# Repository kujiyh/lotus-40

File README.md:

# The Lotus40

The Lotus40 is a 40% keyboard featuring a custom layout, 128x32 OLED display, and QMK/VIA compatible.

I made this project as a way to familiarize myself more with the tools used to create these types of projects. Designing schematics, pcbs, and 3d modelling are all skills I want to get a good grasp on before attempting larger projects, and I view this keyboard as a stepping stone toward that goal.

# Gallery:

Schematic: 

PCB: 

Case: 

BOM:

| Name | Price (CAD) | Link |
| ---- | ----------- | ---- |
| PCB | $31.23 | [link](https://jlc3dp.com/) |
| Arduino | $5.72 | [link](https://www.aliexpress.com/item/1005005301005280.html?spm=a2g0o.productlist.main.1.6a4b6adeVmQufJ&algo_pvid=7472923b-41cf-407d-b425-a25c0e5c7b78&algo_exp_id=7472923b-41cf-407d-b425-a25c0e5c7b78-0&pdp_ext_f=%7B%22order%22%3A%221238%22%2C%22eval%22%3A%221%22%7D&pdp_npi=4%40dis%21CAD%213.04%211.38%21%21%212.18%210.99%21%402103247417511484507088946efacb%2112000032548039884%21sea%21CA%213075130259%21ACX&curPageLogUid=aoXQ197SK8RL&utparam-url=scene%3Asearch%7Cquery_from%3A#nav-description) |
| 128x32 OLED | $3.04 | [link](https://www.aliexpress.com/item/32846843498.html?spm=a2g0o.productlist.main.3.197232b8AfM6ff&algo_pvid=e76c96bb-b016-43db-9c34-8d52bbce9ac0&algo_exp_id=e76c96bb-b016-43db-9c34-8d52bbce9ac0-2&pdp_ext_f=%7B%22order%22%3A%221117%22%2C%22eval%22%3A%221%22%7D&pdp_npi=4%40dis%21CAD%215.82%211.38%21%21%214.17%210.99%21%402101c5b217511483671288564eca8d%2166359327705%21sea%21CA%213075130259%21ACX&curPageLogUid=ZFDLwnG33cxY&utparam-url=scene%3Asearch%7Cquery_from%3A) |
| Keycaps | $26.63 | [link](https://www.aliexpress.com/item/1005006200329301.html?spm=a2g0o.productlist.main.17.3f144d54IWFfw4&algo_pvid=d3da5403-813b-40e9-b3a1-3665eacd772a&algo_exp_id=d3da5403-813b-40e9-b3a1-3665eacd772a-16&pdp_ext_f=%7B%22order%22%3A%22129%22%2C%22eval%22%3A%221%22%7D&pdp_npi=4%40dis%21CAD%2132.86%2114.08%21%21%2123.34%2110.00%21%402101ea8c17507209741814895e95c4%2112000043031474456%21sea%21CA%213075130259%21ACX&curPageLogUid=D2UwlqdSg0RB&utparam-url=scene%3Asearch%7Cquery_from%3A) |
| Switches | $24.52 | [link](https://www.aliexpress.com/item/1005008394917920.html?spm=a2g0o.productlist.main.1.645353acpb1uSd&algo_pvid=0f13a266-3646-45ba-9601-fa8c88c5af20&algo_exp_id=0f13a266-3646-45ba-9601-fa8c88c5af20-0&pdp_ext_f=%7B%22order%22%3A%2240%22%2C%22eval%22%3A%221%22%7D&pdp_npi=4%40dis%21CAD%2111.29%212.35%21%21%218.09%211.68%21%402103245417511474735238088eae82%2112000044841496191%21sea%21CA%213075130259%21ACX&curPageLogUid=mx57PwAEfzUi&utparam-url=scene%3Asearch%7Cquery_from%3A) |
| Stabiliizers | $11.76 | [link](https://www.aliexpress.com/item/1005006528731543.html?spm=a2g0o.productlist.main.1.64403b4bSXKdtR&algo_pvid=2a392ca5-f9b7-4640-a01c-664826ab7547&algo_exp_id=2a392ca5-f9b7-4640-a01c-664826ab7547-0&pdp_ext_f=%7B%22order%22%3A%22924%22%2C%22eval%22%3A%221%22%7D&pdp_npi=4%40dis%21CAD%2111.76%215.48%21%21%218.43%213.93%21%402103010b17511455687663518e23c7%2112000037543723481%21sea%21CA%213075130259%21ACX&curPageLogUid=qf7Fg803iAUK&utparam-url=scene%3Asearch%7Cquery_from%3A) |

Total Price in CAD/USD: $103.27/$75.38

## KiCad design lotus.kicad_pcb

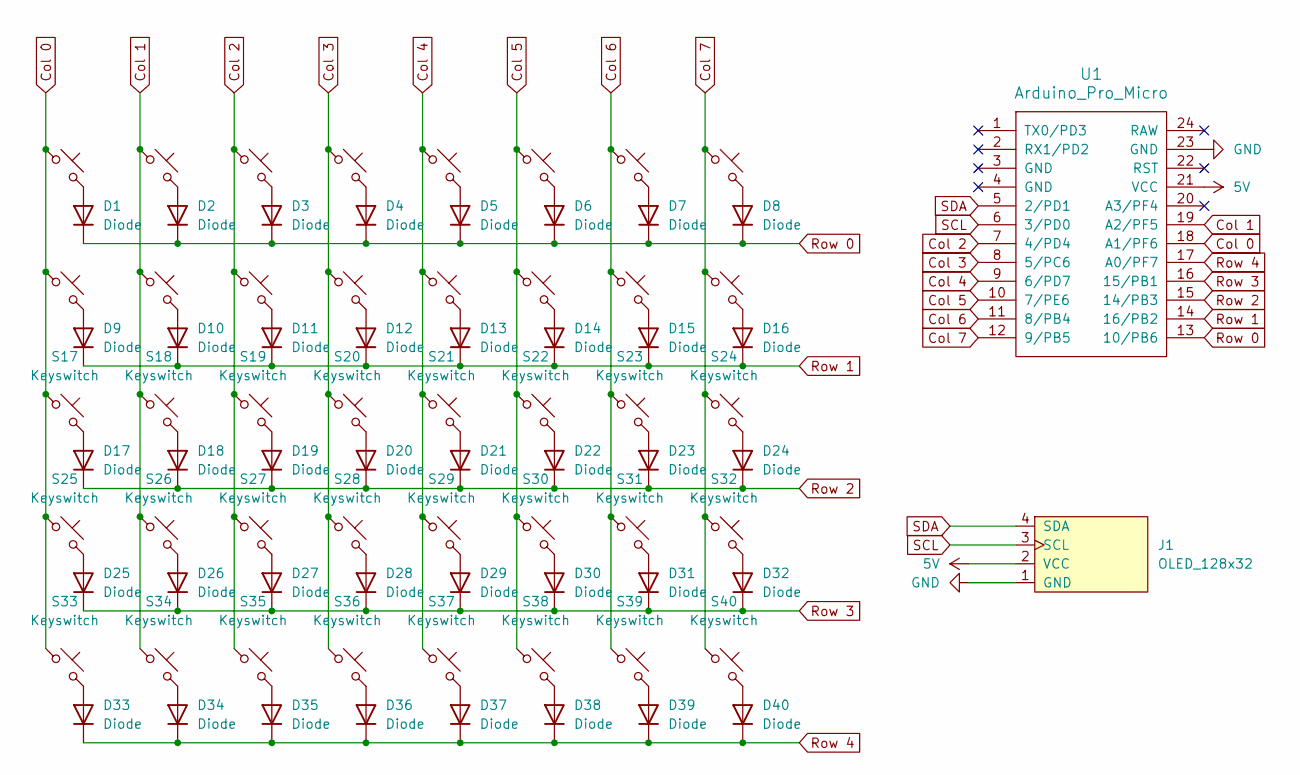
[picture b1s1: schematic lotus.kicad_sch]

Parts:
D1, D2, D3, D4, D5, D6, D7, D8, D9, D10, D11, D12, D13, D14, D15, D16, D17, D18, D19, D20, D21, D22, D23, D24, D25, D26, D27, D28, D29, D30, D31, D32, D33, D34, D35, D36, D37, D38, D39, D40: Diode; Diode_DO-35
J1: OLED_128x32
S1, S2, S3, S4, S5, S6, S7, S8, S9, S10, S11, S12, S13, S14, S15, S16, S17, S18, S19, S20, S21, S22, S23, S24, S25, S26, S27, S28, S29, S30, S31, S32, S33, S34, S35, S36, S37, S38, S39, S40: Keyswitch; MX_PCB_1.00u
U1: Arduino_Pro_Micro

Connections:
5V: J1.2 (VCC), U1.21 (VCC)
Col 0: S1.1, S9.1, S17.1, S25.1, S33.1, U1.18 (A1/PF6)
Col 1: S2.1, S10.1, S18.1, S26.1, S34.1, U1.19 (A2/PF5)
Col 2: S3.1, S11.1, S19.1, S27.1, S35.1, U1.7 (4/PD4)
Col 3: S4.1, S12.1, S20.1, S28.1, S36.1, U1.8 (5/PC6)
Col 4: S5.1, S13.1, S21.1, S29.1, S37.1, U1.9 (6/PD7)
Col 5: S6.1, S14.1, S22.1, S30.1, S38.1, U1.10 (7/PE6)
Col 6: S7.1, S15.1, S23.1, S31.1, S39.1, U1.11 (8/PB4)
Col 7: S8.1, S16.1, S24.1, S32.1, S40.1, U1.12 (9/PB5)
GND: J1.1 (GND), U1.23 (GND)
unnamed: D1.2 (A), S1.2
unnamed: D2.2 (A), S2.2
unnamed: D3.2 (A), S3.2
unnamed: D4.2 (A), S4.2
unnamed: D5.2 (A), S5.2
unnamed: D6.2 (A), S6.2
unnamed: D7.2 (A), S7.2
unnamed: D8.2 (A), S8.2
unnamed: D9.2 (A), S9.2
unnamed: D10.2 (A), S10.2
unnamed: D11.2 (A), S11.2
unnamed: D12.2 (A), S12.2
unnamed: D13.2 (A), S13.2
unnamed: D14.2 (A), S14.2
unnamed: D15.2 (A), S15.2
unnamed: D16.2 (A), S16.2
unnamed: D17.2 (A), S17.2
unnamed: D18.2 (A), S18.2
unnamed: D19.2 (A), S19.2
unnamed: D20.2 (A), S20.2
unnamed: D21.2 (A), S21.2
unnamed: D22.2 (A), S22.2
unnamed: D23.2 (A), S23.2
unnamed: D24.2 (A), S24.2
unnamed: D25.2 (A), S25.2
unnamed: D26.2 (A), S26.2
unnamed: D27.2 (A), S27.2
unnamed: D28.2 (A), S28.2
unnamed: D29.2 (A), S29.2
unnamed: D30.2 (A), S30.2
unnamed: D31.2 (A), S31.2
unnamed: D32.2 (A), S32.2
unnamed: D33.2 (A), S33.2
unnamed: D34.2 (A), S34.2
unnamed: D35.2 (A), S35.2
unnamed: D36.2 (A), S36.2
unnamed: D37.2 (A), S37.2
unnamed: D38.2 (A), S38.2
unnamed: D39.2 (A), S39.2
unnamed: D40.2 (A), S40.2
Row 0: D1.1 (K), D2.1 (K), D3.1 (K), D4.1 (K), D5.1 (K), D6.1 (K), D7.1 (K), D8.1 (K), U1.13 (10/PB6)
Row 1: D9.1 (K), D10.1 (K), D11.1 (K), D12.1 (K), D13.1 (K), D14.1 (K), D15.1 (K), D16.1 (K), U1.14 (16/PB2)
Row 2: D17.1 (K), D18.1 (K), D19.1 (K), D20.1 (K), D21.1 (K), D22.1 (K), D23.1 (K), D24.1 (K), U1.15 (14/PB3)
Row 3: D25.1 (K), D26.1 (K), D27.1 (K), D28.1 (K), D29.1 (K), D30.1 (K), D31.1 (K), D32.1 (K), U1.16 (15/PB1)
Row 4: D33.1 (K), D34.1 (K), D35.1 (K), D36.1 (K), D37.1 (K), D38.1 (K), D39.1 (K), D40.1 (K), U1.17 (A0/PF7)
SCL: J1.3 (SCL), U1.6 (3/PD0)
SDA: J1.4 (SDA), U1.5 (2/PD1)

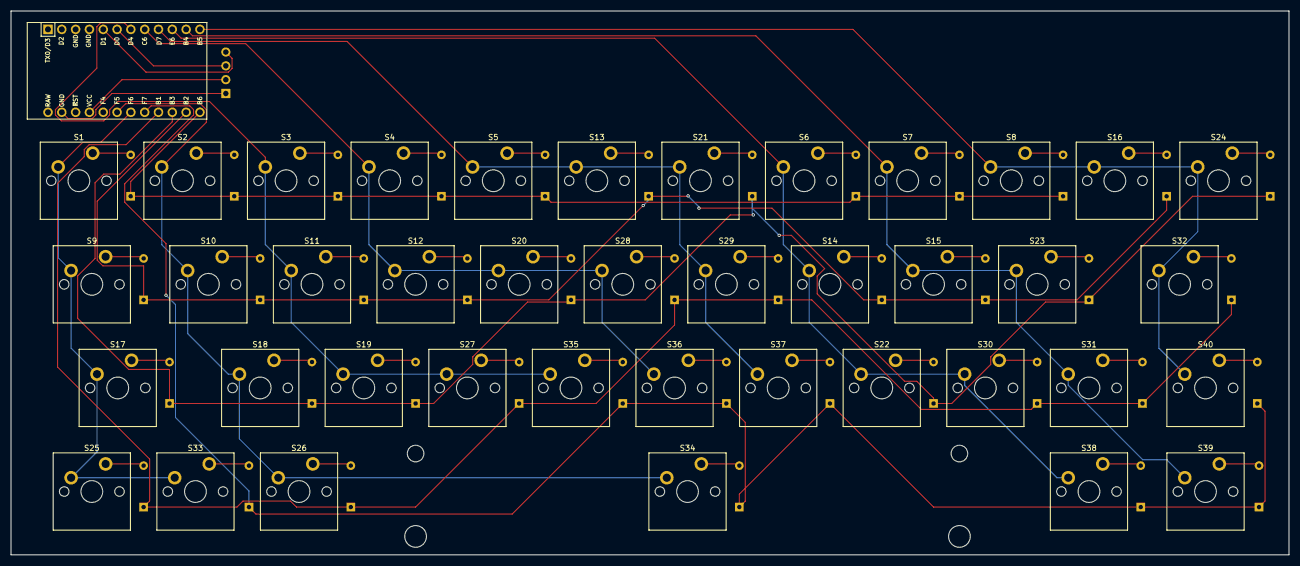
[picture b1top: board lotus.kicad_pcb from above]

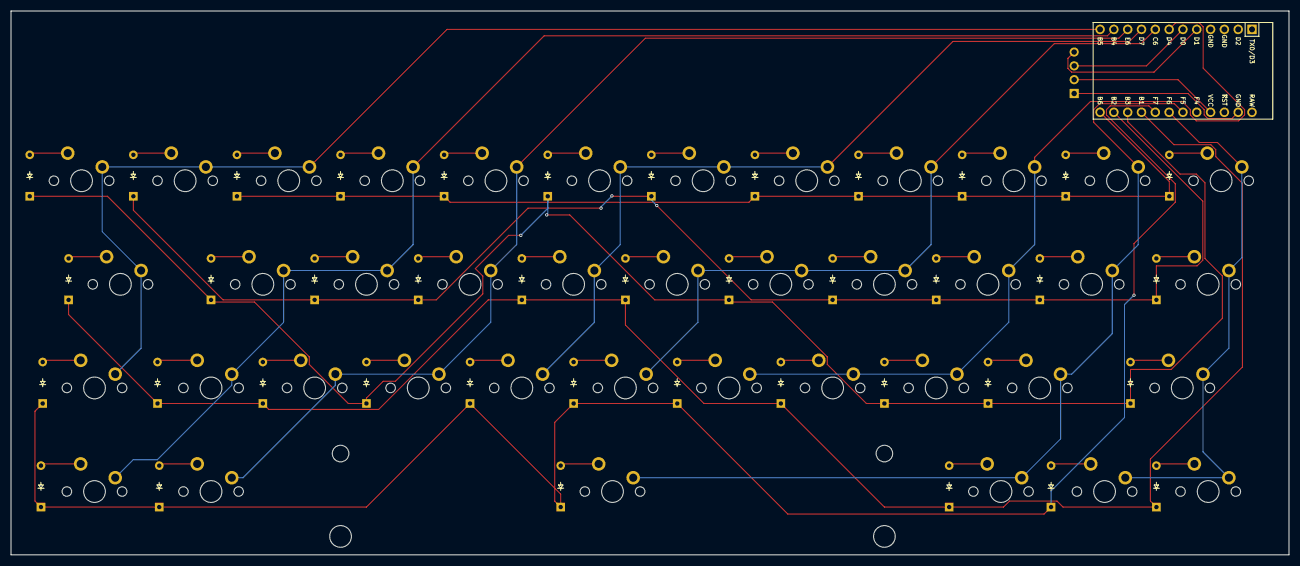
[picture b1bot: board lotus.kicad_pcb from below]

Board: 2 copper layers, 235.0 x 100.0 mm, 82 parts (41 on the bottom side), 57 nets.

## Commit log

2025-06-25 Create file
2025-06-28 Added CAD files
2025-06-28 bill of materials
2025-06-28 Added keyboard case STL
2025-06-28 Create firmware
2025-07-01 Create temp
2025-07-02 added firmware code
    does not contain OLED firmware
2025-09-10 firmware
